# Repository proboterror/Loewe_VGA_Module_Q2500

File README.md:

# Loewe TVs Q2500 VGA Module
Recreation of VGA module PCB for Loewe TVs with Q2500M chassis.

Project based on work done by Oelii from [circuit-board.de/forum](https://circuit-board.de/forum/index.php/Thread/28516-WIP-DIY-Loewe-VGA-Modul-Q2500/)

Schematic recreated from the scratch in KiCad. PCB based on Oelii's layout and verified with Desing/Electrical Rules Checker tools.<br>
Components footprints replaced with KiCad standard ones.

## Chassis compatibility
Unverified, obtained from post by djcalle on [circuit-board.de/forum](https://circuit-board.de/forum/index.php/Thread/28516-WIP-DIY-Loewe-VGA-Modul-Q2500/?postID=906980#post906980):
- Q23, Q24, Q25 can accept VGA cards.
- Q25 and Q24 use the same VGA card (only 2 differences: cable length and 150R termination on RGB lines.)
- Q25 seems to be inconsistent with VGA card compatibility.
- Q24 seems consistent with vga card compatibility.
- Q23 uses its own [different card](https://github.com/proboterror/Loewe_VGA_Module_Q2300).

## EDID option
For widescreen TVs [EDID](https://en.wikipedia.org/wiki/Extended_Display_Identification_Data) EEPROM option can be installed and flashed, helping to automatically add 848x480@60Hz (CVT) default widescreen resolution.

Original schematic from [Loewe Q2500-M chassis service manual](doc/Q2500-M/Loewe%20Q2500M%20Service%20Manual.pdf)

Recreated schematic and PCB

## Bill of materials
|Reference|Value|Footprint|Qty|
|-----|-----|-----|-----|
|C811,C817,C826,C828,C829|100n|0805|5|
|C813,C814,C821,C827|10p|0805|4|
|C816|10u|0805|1|
|C818|22n|0805|1|
|C822|100p|0805|1|
|L816,L826|1210(3225)|4.7uH|2|
|R814,R819,R821,R823,R828,R829|100R|0805|6|
|R817|10k|0805|1|
|R818|1k|0805|1|
|R827|47k|0805|1|
|R836,R837,R838|150R|0805|3|
|I811|74HCT86|SO-14|1|
|W801|VGA DSUB-15<br>Edge pin offset 8.35mm<br>Mounting holes offset 10.89mm ||1|
|W831|JST XH 2.54 12 Pin||1|
|U2|AT24C02 (EDID option)|SOIC-8|1|
|R1,R2|2K2 (EDID option)|0805|2|

## Order boards from manufacturer
Send "gerbers" folder content packed to zip archive.

## Build Notes
AT24C02 EEPROM and R1,R2 are EDID option, useful for connection widescreen models to PC/VGA.

L816 and L826 SMD 1210(3225) inductors value are unknown; 4.7uH in Q2300 VGA module schematic; can be replaced with 0R resistor.

W831 connector originally is Molex 22-23-2121. Probably can be replaced with XH 2.54 12 pin connectors / cables, note pins step 2.5/254 mm.<br>
Pay attention on cable connectors type: same direction or reverse direction.<br>
12 pin 50 cm cable are required for Q25 chassis, 30 cm cable for Q24 chassis. For Q23 chassis, two 10 pin cables are required.

**Double-check ground and VCC connection on VGA module PCB and TV chassis before soldering 12-pin W831 connector and power on.**

## EDID ROM
[Extended Display Identification Data (EDID)](https://en.wikipedia.org/wiki/Extended_Display_Identification_Data) ROM sends display info to PC over VGA [I2C](https://en.wikipedia.org/wiki/I2C) [DDC (Display Data Channel)](https://en.wikipedia.org/wiki/Display_Data_Channel), such as supported / default resolutions, supported frequency ranges, physical dimensions and display name.

Standard VGA resolutions 640x400@70Hz and 640x480@60Hz marked as supported.<br>
Added custom default resolution 848x480@60Hz.<br>
Added modeline generated with [CVT](doc/VESA-CVT-1.2.pdf) formulas.<br>
Display reported as "Loewe CRT".

Generated [edid.bin](EDID/edid.bin) can be in-system programmed to AT24C02 EEPROM with CH341 (I2C) programmer, 8 pin chip clip and NeoProgrammer V2.2.0.10:
"IC/I2C/Generic/_24C02 [3.3V]" or "Detect", "File/Open" .bin, "Write IC" (Erase, Blank Check, Write, Verify).

[EDID 1.3](doc/VESA-EEDID-A1.pdf) display description ROM image in raw .hex format generated with [generate_edid.py](EDID/generate_edid.py) script.

Generate edid.hex:
```
python generate_edid.py > edid.hex
```
Convert raw .hex to .bin:
```
type edid.hex | xxd -r -p > edid.bin
```
To view generated display description:
```
edid-decode edid.bin
```

Conservative / more compatible custom modeline included by default:
```
Modeline "848x480_60" 31.75  848 864 944 1024  480 483 493 517 -hsync +vsync
```
Alternative modeline generated with cvt utility can be selected in generate_edid.py:
```
cvt 848 480 60
Modeline "848x480_60" 31.50  848 872 952 1056  480 483 493 500 -hsync +vsync
```

## Install
Q2400 chassis:

Q2500 chassis:

## Required TV and adapter board modifications
Mods information provided by @neonname.

Combined VGA adapter board output and TV input termination/load resistance for RGB lines should be ~75 Ohm.

### Q2400
TV Signal Board schematic:

PCB components side:

Q2400 signal board already have 75 Ohm termination resistors on RGB lines.<br>
150 Ohm RGB termination resistors on adapter board should be removed.
<hr>

### Q2500-B
TV Signal Board schematic:

PCB components side:

PCB solder side:

PCB missing W1011 VGA connector and RGB input resistors, RGB input connected to ground with 0R load resistors.<br>
Suggested changes, needs to check on real board:<br>
- Replaсe R2641, R2643, R2646 (0R) with 27R, add missing R1016, R1017, R1018 47R resistors (like Q2500-M) (probably incorrect termination)
- Or replaсe R2641, R2643, R2646 (0R) with 150R; add missing R1016, R1017, R1018 (0R) (like Q2500-H). Note: R2512, R2513, R2514.
<hr>

### Q2500-H
TV Signal Board schematic:

PCB components side:

PCB solder side:

Recommended changes:<br>
- Replaсe R2641, R2643, R2646 (68R) with 150R; R1016, R1017, R1018 (10R) with 0R; R2512, R2513, R2514 (0R) with 47R; remove C1016, C1017, C1018.
<hr>

### Q2500-M
TV Signal Board schematic:

PCB components side:

PCB solder side:

Suggested changes, needs to check on real board:<br>
- Replaсe R2641, R2643, R2646 (47R) with 150R; R1016, R1017, R1018 (27R) with 0R; remove C1016, C1017, C1018. Note: R2512, R2513, R2514.
<hr>

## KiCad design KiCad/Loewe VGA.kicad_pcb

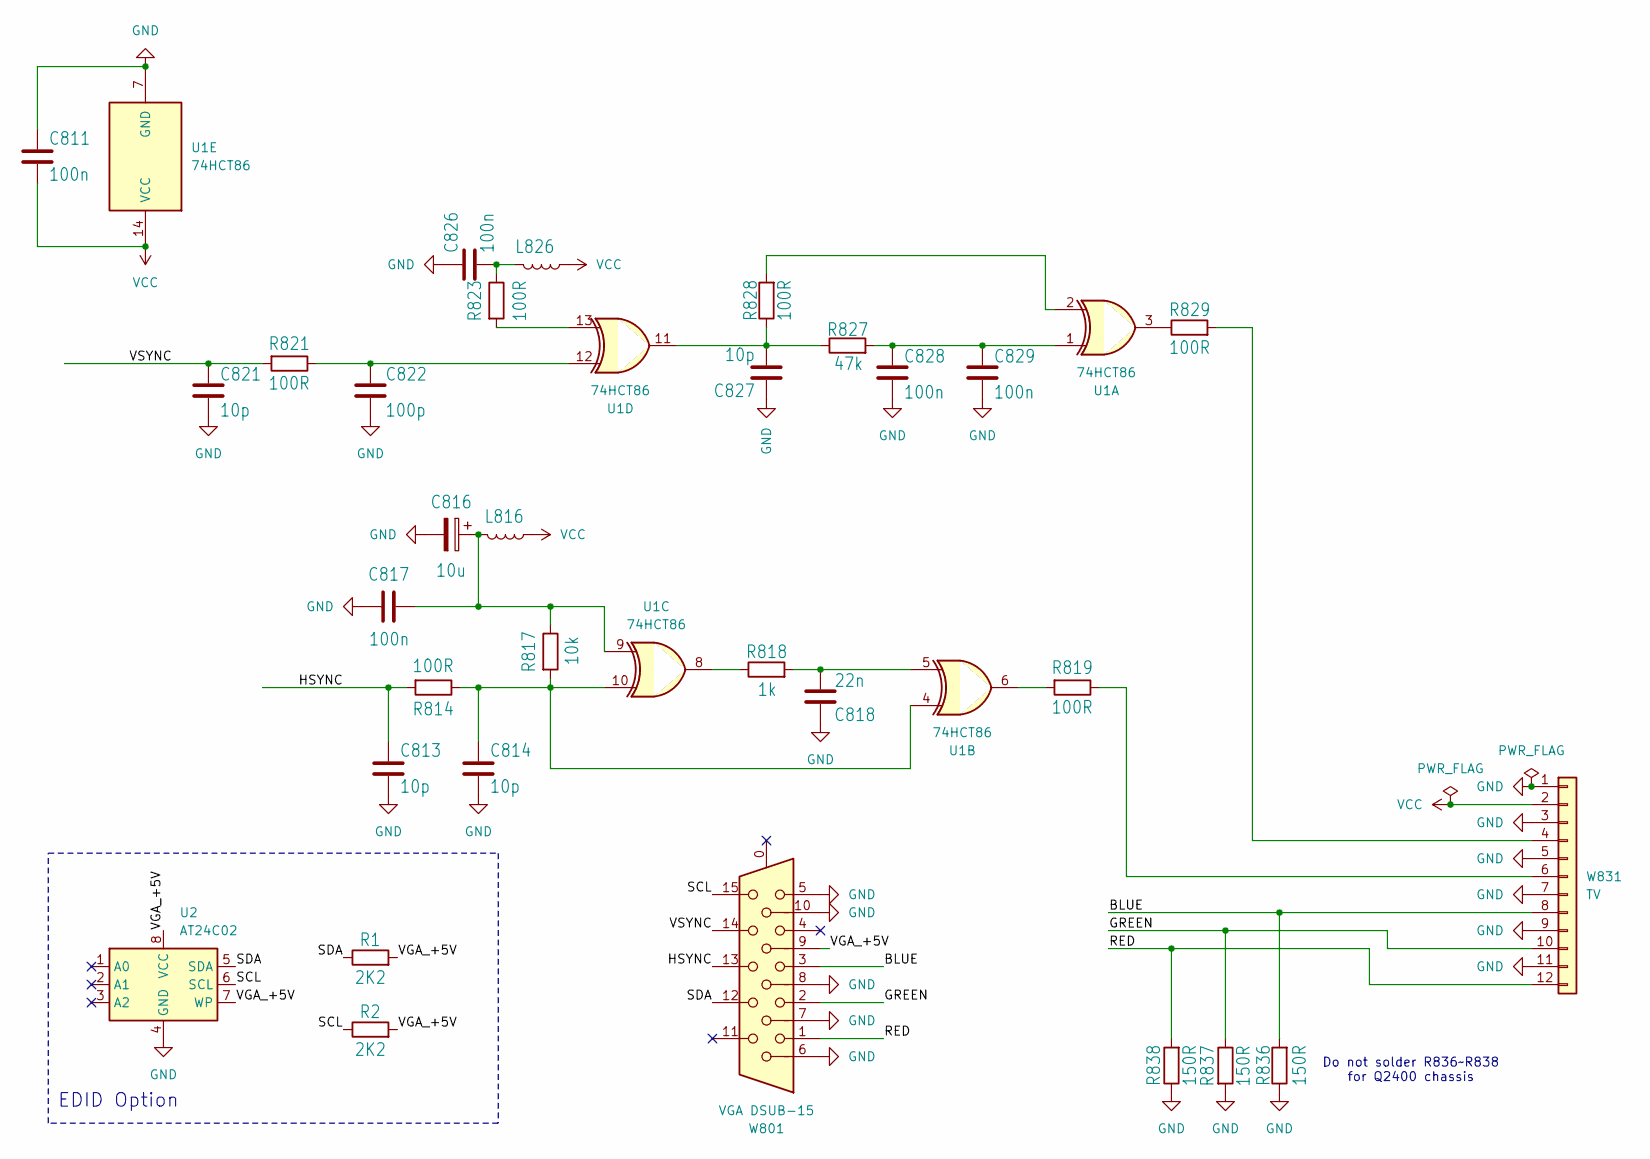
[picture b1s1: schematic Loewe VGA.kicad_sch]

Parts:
C811, C817, C826, C828, C829: 100n; C_0805_2012Metric_Pad1.18x1.45mm_HandSolder
C813, C814, C821, C827: 10p; C_0805_2012Metric_Pad1.18x1.45mm_HandSolder
C816: 10u; CP_Elec_6.3x5.3
C818: 22n; C_0805_2012Metric_Pad1.18x1.45mm_HandSolder
C822: 100p; C_0805_2012Metric_Pad1.18x1.45mm_HandSolder
L816, L826: 4u7; L_1210_3225Metric_Pad1.42x2.65mm_HandSolder
R1, R2: 2K2; R_0805_2012Metric_Pad1.20x1.40mm_HandSolder
R814, R819, R821, R823, R828, R829: 100R; R_0805_2012Metric_Pad1.20x1.40mm_HandSolder
R817: 10k; R_0805_2012Metric_Pad1.20x1.40mm_HandSolder
R818: 1k; R_0805_2012Metric_Pad1.20x1.40mm_HandSolder
R827: 47k; R_0805_2012Metric_Pad1.20x1.40mm_HandSolder
R836, R837, R838: 150R; R_0805_2012Metric_Pad1.20x1.40mm_HandSolder
U1: 74HCT86; SO-14_3.9x8.65mm_P1.27mm
U2: AT24C02; SOIC-8_3.9x4.9mm_P1.27mm
W801: VGA DSUB-15; DSUB-15-HD_Female_Horizontal_P2.29x1.98mm_EdgePinOffset3.03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
W831: TV; JST_XH_B12B-XH-A_1x12_P2.54mm_Vertical

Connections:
/BLUE: R836.2, W801.3, W831.8
/GREEN: R837.1, W801.2, W831.10
/HSYNC: C813.1, R814.2, W801.13
/RED: R838.2, W801.1, W831.12
/SCL: R2.1, U2.6 (SCL), W801.15
/SDA: R1.1, U2.5 (SDA), W801.12
/VGA_+5V: R1.2, R2.2, U2.7 (WP), U2.8 (VCC), W801.9
/VSYNC: C821.1, R821.2, W801.14
GND: C811.1, C813.2, C814.2, C816.2, C817.1, C818.1, C821.2, C822.2, C826.1, C827.1, C828.2, C829.2, R836.1, R837.2, R838.1, U1.7 (GND), U2.4 (GND), W801.5, W801.6, W801.7, W801.8, W801.10, W831.1, W831.3, W831.5, W831.7, W831.9, W831.11
unnamed: C814.1, R814.1, R817.2, U1.4, U1.10
unnamed: C816.1, C817.2, L816.2, R817.1, U1.9
unnamed: C818.2, R818.2, U1.5
unnamed: C822.1, R821.1, U1.12
unnamed: C826.2, L826.2, R823.1
unnamed: C827.2, R827.1, R828.1, U1.11
unnamed: C828.1, C829.1, R827.2, U1.1
unnamed: R818.1, U1.8
unnamed: R819.2, U1.6
unnamed: R823.2, U1.13
unnamed: R828.2, U1.2
unnamed: R829.1, U1.3
unnamed: R829.2, W831.4
unnamed: R819.1, W831.6
VCC: C811.2, L816.1, L826.1, U1.14 (VCC), W831.2

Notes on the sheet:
EDID Option
Do not solder R836~R838 for Q2400 chassis

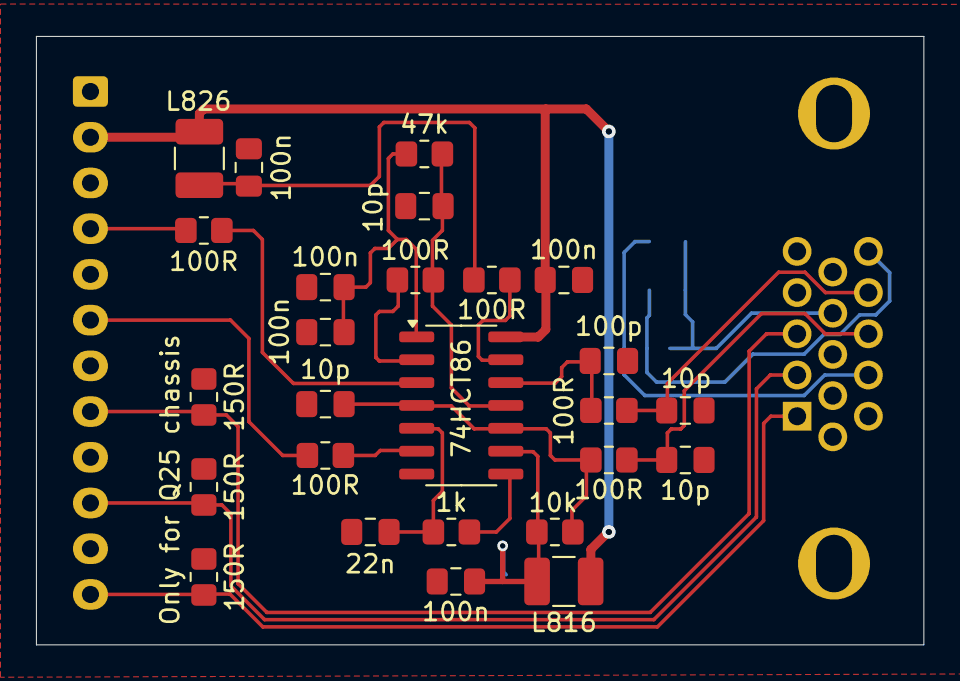
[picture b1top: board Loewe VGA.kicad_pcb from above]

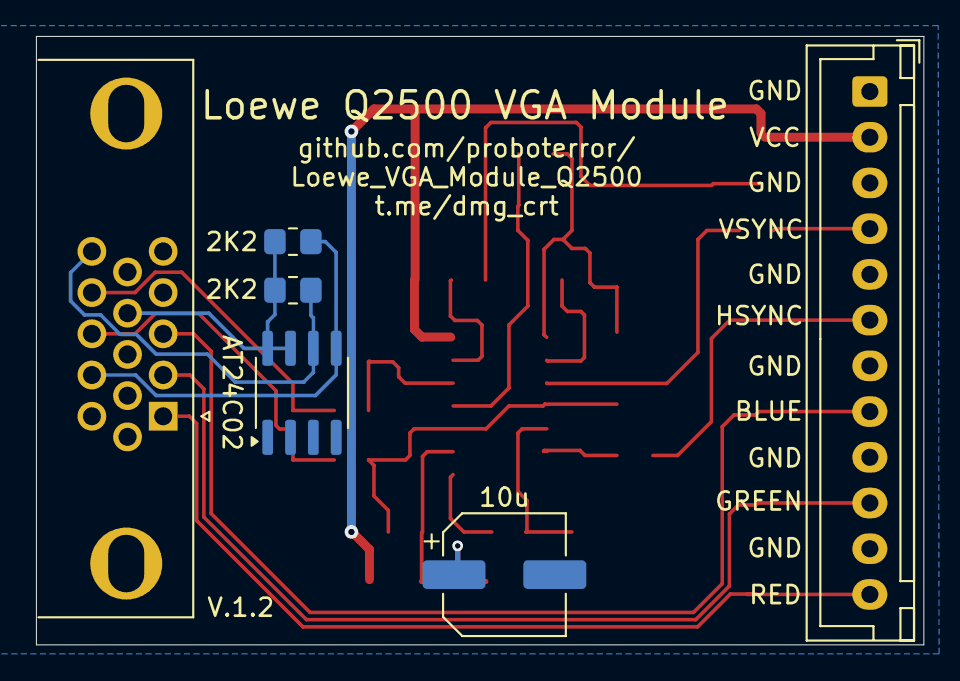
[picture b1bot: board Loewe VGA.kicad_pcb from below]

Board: 2 copper layers, 49.3 x 33.8 mm, 32 parts (6 on the bottom side), 24 nets.

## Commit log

2025-10-24 Initial KiCad project PCB implementation.
    Original project from https://circuit-board.de/forum/index.php/Thread/28516-WIP-DIY-Loewe-VGA-Modul-Q2500/
    Schematic and PCB imported from Eagle.
    Schematic recreated from service manual.
    Footprints for C, R, 74HCT86, DSUB-15 replaced with standard KiCad ones.
    PCB altered for new footprints. Tracks width increased to 0.2 mm.
    Schematic and PCB checked with Electrical / Design Rules Checker.
2025-10-24 Add project description.
2025-10-24 Alter silkscreen labels.
2025-10-24 Alter VGA DSUB-15 connector mounting holes.
2025-10-24 Add gerber fabrication output.
2025-11-06 Add project title and link to PCB silkscreen.
2025-11-06 Production gerbers.
2025-11-13 Connect VGA pin 8 to GND.
2025-11-13 Add Loewe Q2400 Chassis Service Manual.
2025-11-13 Do not solder R836~R838 RGB input termination resistors for Q2400 chassis. Source: Loewe Q2400 service manual, p.2-22.
2025-11-14 Add Q2300 VGA module link.
2025-11-16 Update README.md.
2025-11-16 Replace custom 3225 footprint for L826, L816 with standard 1210(3225). Add 4.7uH value for L826, L816 to schematic (use value from Q2300 board).
2025-11-16 Add telegram channel link. Adjust power tracks width.
2025-11-16 Add R836~R838 RGB termination resistors note on PCB silkscreen.
2025-11-16 Add connection diagram for Q2400 chassis.
2025-11-16 Add connection diagram for Q2500 chassis.
2025-11-16 Replace Q2500M service manual with complete version.
2025-11-22 Add non-standard 2.54 mm JST XH S12B connector footprint based on KiCad 2.50 mm one.
2025-11-22 Replace JST XH 2.50 mm with custom 2.54 mm. Remove unused Molex 22-23-2121 footprint. Add version V.1.1 label to PCB silkscreen.
2025-11-22 Update PCB images.
2025-12-14 Replace incorrect Connector_Dsub:DSUB-15-HD_Male with short Connector_Dsub:DSUB-15-HD_Female. Move VGA and TV connectors to back side. Reduce PCB width. Change VCC tracks width from 0.3 to 0.5 mm. Al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
    PCB version updated to 1.2.
2025-12-14 Update gerbers.
2025-12-15 Arrange docs.
2025-12-15 Arrange Q2400 docs, add service manual with signal board schematic.
2025-12-15 Add Q2400 mod info.
2025-12-15 Add Q2500 signal boards schematics.
2025-12-15 Add Q2500-M PCB images.
2025-12-15 Add Q2500-H PCB images.
2025-12-15 Add Q2500-B PCB images.
2025-12-15 Add PCB input termination mods description.
2025-12-15 Add PCB service manuals drawings for Q2500-B, Q2500-H.
2026-05-08 Add Q2400 Signal Board PCB image to description.
2026-05-08 Add "Technology of Q2500 colour TV set" to documentation.
2026-05-08 Add TDA933xH datasheet.
2026-06-22 Add EDID EEPROM option for 848x480@60Hz mode auto detection with widescreen TVs.
    PCB version 1.2.
